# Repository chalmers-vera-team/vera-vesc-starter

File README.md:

# Vera — Starter Motor System

Custom VESC 6-based motor controller developed for the **Vera** Shell Eco-marathon ICE vehicle. It drives a sensored TP Power TP4050 brushless motor through a 6.67:1 belt reduction to reliably crank a rebuilt Honda GX35 4-stroke engine (900–1,200 RPM) at ultra-low energy consumption (<30 Joules per start).

## Overview

* **HW/**: KiCad design files for the custom 4-layer STM32F405 + TI DRV8323RS motor controller (`HW/vera_vesc_starter.kicad_pro`).
* **SW/**: [VEDDERB BLDC Firmware](https://github.com/vedderb/bldc) tracked as a Git submodule.

## Quick Start

Mjau

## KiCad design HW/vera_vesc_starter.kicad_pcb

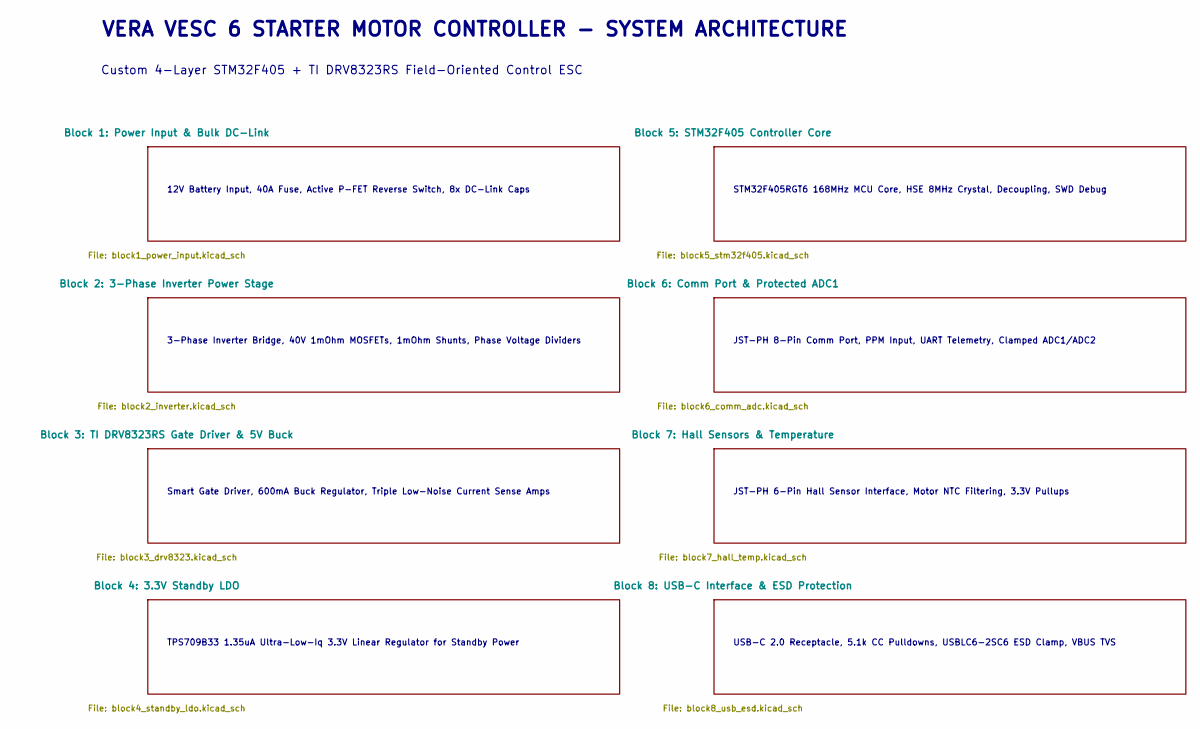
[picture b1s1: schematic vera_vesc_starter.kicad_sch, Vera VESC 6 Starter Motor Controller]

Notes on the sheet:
Smart Gate Driver, 600mA Buck Regulator, Triple Low-Noise Current Sense Amps
TPS709B33 1.35uA Ultra-Low-Iq 3.3V Linear Regulator for Standby Power
USB-C 2.0 Receptacle, 5.1k CC Pulldowns, USBLC6-2SC6 ESD Clamp, VBUS TVS
STM32F405RGT6 168MHz MCU Core, HSE 8MHz Crystal, Decoupling, SWD Debug
Custom 4-Layer STM32F405 + TI DRV8323RS Field-Oriented Control ESC
3-Phase Inverter Bridge, 40V 1mOhm MOSFETs, 1mOhm Shunts, Phase Voltage Dividers
VERA VESC 6 STARTER MOTOR CONTROLLER - SYSTEM ARCHITECTURE
JST-PH 8-Pin Comm Port, PPM Input, UART Telemetry, Clamped ADC1/ADC2
12V Battery Input, 40A Fuse, Active P-FET Reverse Switch, 8x DC-Link Caps
JST-PH 6-Pin Hall Sensor Interface, Motor NTC Filtering, 3.3V Pullups

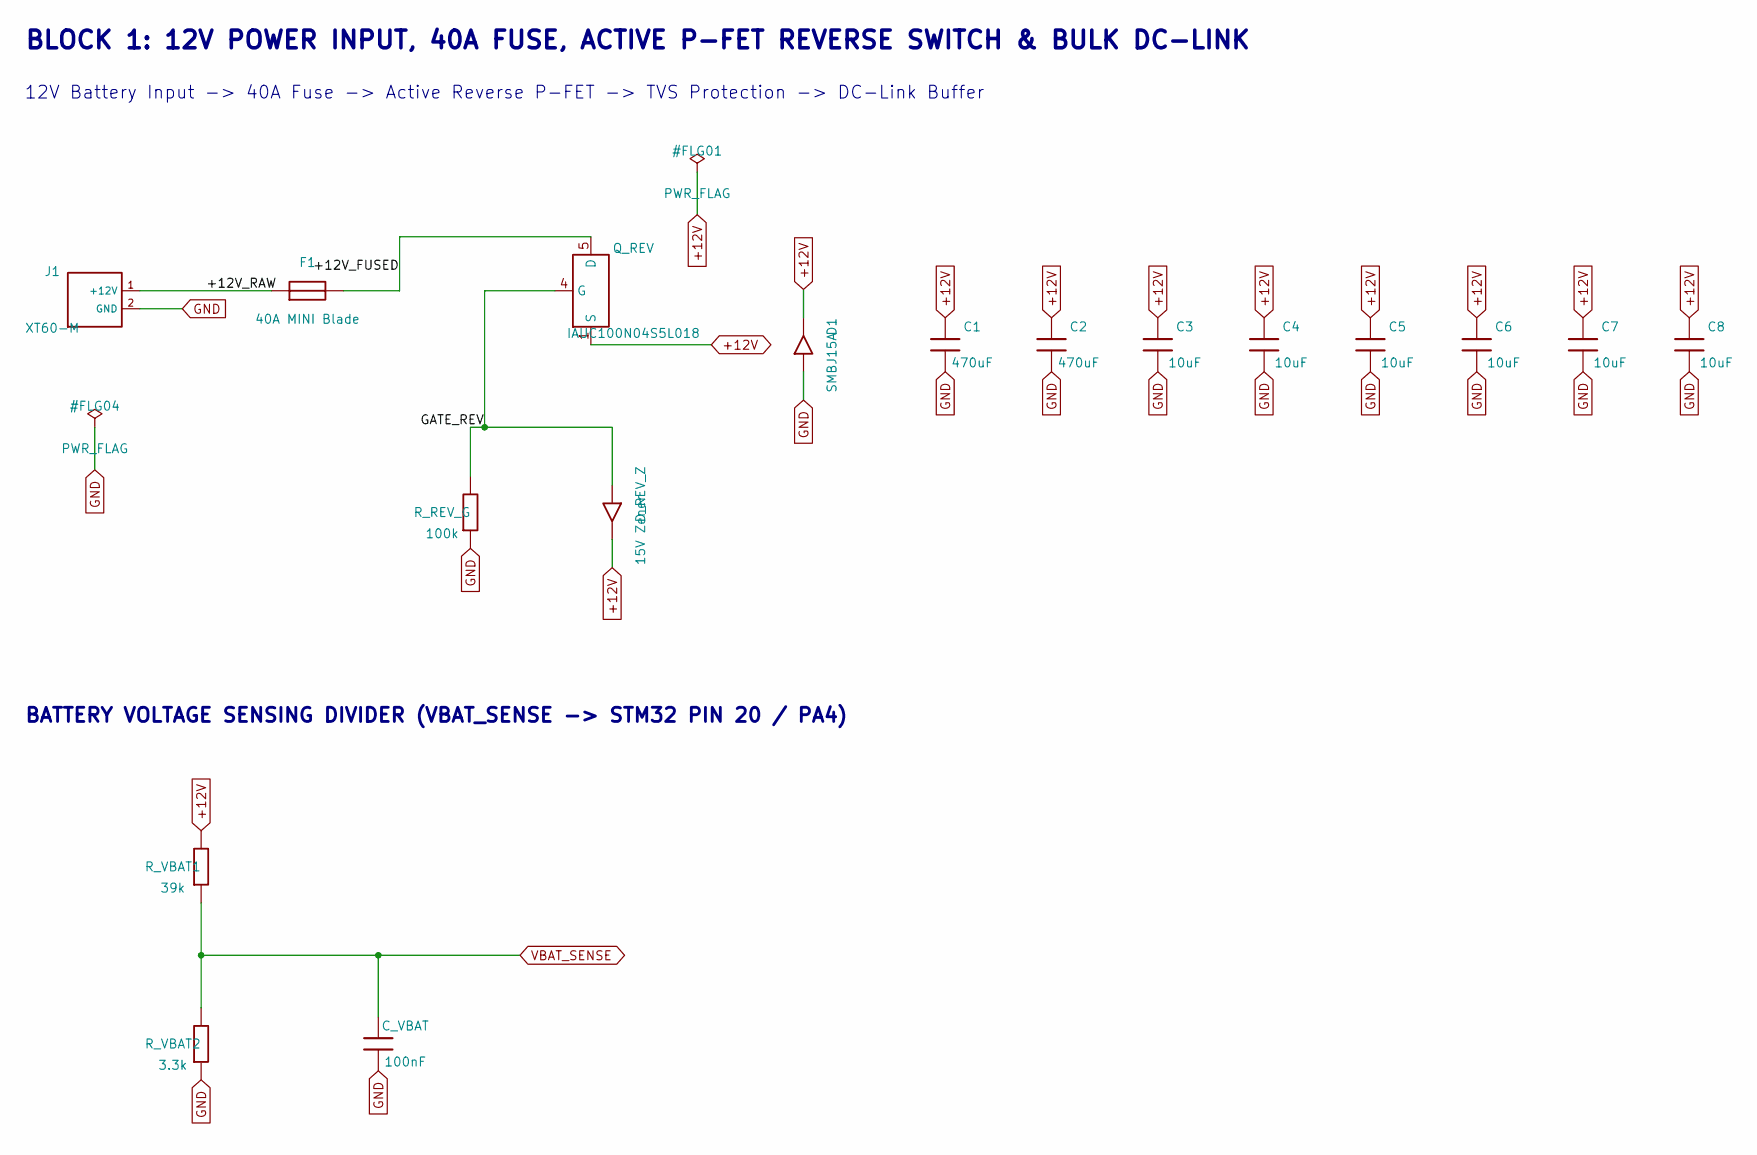
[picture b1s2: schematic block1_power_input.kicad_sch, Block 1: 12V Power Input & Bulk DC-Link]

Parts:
C1, C2: 470uF; CP_Elec_10x10.5; MPN EEH-ZK1V471P
C3, C4, C5, C6, C7, C8: 10uF; C_1206_3216Metric; MPN C1206C106K5RAC7800
C_VBAT: 100nF; C_0603_1608Metric; MPN CC0603KRX7R9BB104
D1: SMBJ15A; D_SMB; MPN SMBJ15A-E3/52
D_REV_Z: 15V Zener; D_SOD-123; MPN MMSZ5245B
F1: 40A MINI Blade; Fuseholder_Blade_Mini_Keystone_3568; MPN Keystone 3568
J1: XT60-M; AMASS_XT60-M_1x02_P7.20mm_Vertical; MPN AMASS-XT60-M
Q_REV: IAUC100N04S5L018; Infineon_PG-TDSON-8_6.15x5.15mm; MPN IAUC100N04S5L018
R_REV_G: 100k; R_0603_1608Metric; MPN RC0603FR-07100KL
R_VBAT1: 39k; R_0603_1608Metric; MPN RC0603FR-0739KL
R_VBAT2: 3.3k; R_0603_1608Metric; MPN RC0603FR-073K3L

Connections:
+12V: C1.1, C2.1, C3.1, C4.1, C5.1, C6.1, C7.1, C8.1, D1.2 (K), D_REV_Z.2 (K), Q_REV.1 (S), Q_REV.2, Q_REV.3, R_VBAT1.1; also elsewhere on the board
+12V_FUSED: F1.2, Q_REV.5 (D)
+12V_RAW: F1.1, J1.1 (+12V)
GATE_REV: D_REV_Z.1 (A), Q_REV.4 (G), R_REV_G.1
GND: C1.2, C2.2, C3.2, C4.2, C5.2, C6.2, C7.2, C8.2, C_VBAT.2, D1.1 (A), J1.2 (GND), R_REV_G.2, R_VBAT2.2; also elsewhere on the board
VBAT_SENSE: C_VBAT.1, R_VBAT1.2, R_VBAT2.1; also elsewhere on the board

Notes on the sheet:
12V Battery Input -> 40A Fuse -> Active Reverse P-FET -> TVS Protection -> DC-Link Buffer
BATTERY VOLTAGE SENSING DIVIDER (VBAT_SENSE -> STM32 PIN 20 / PA4)
BLOCK 1: 12V POWER INPUT, 40A FUSE, ACTIVE P-FET REVERSE SWITCH & BULK DC-LINK

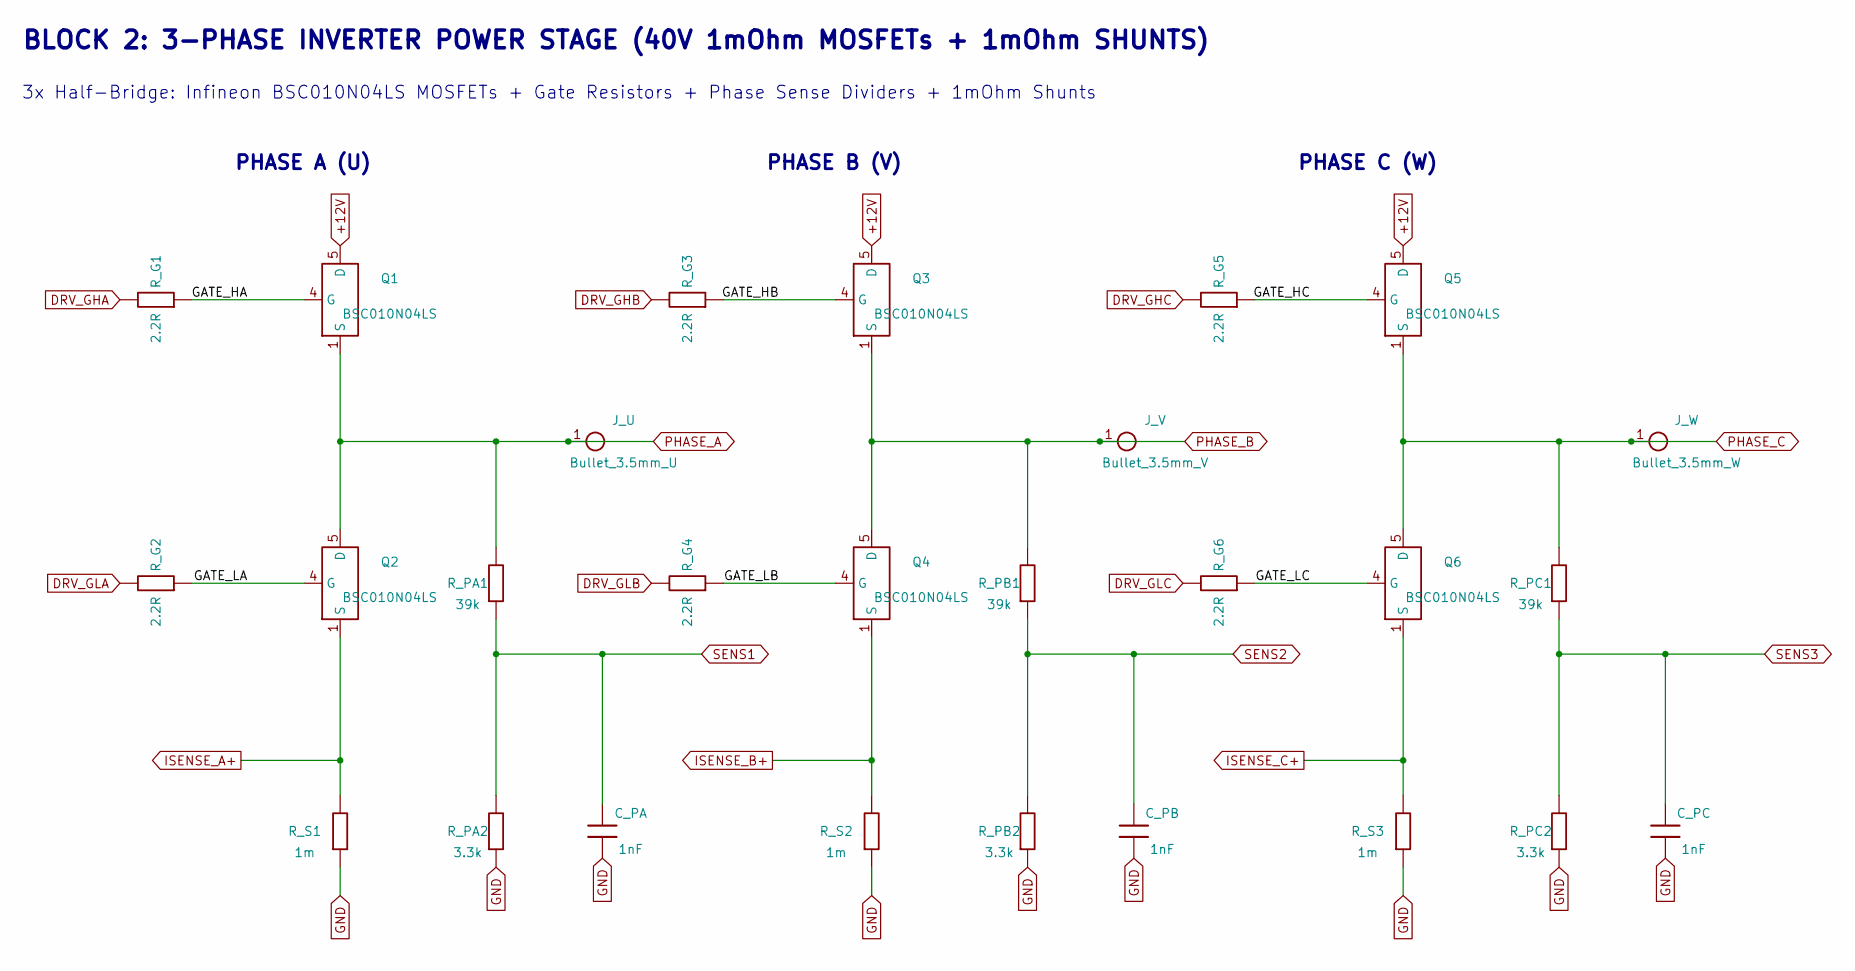
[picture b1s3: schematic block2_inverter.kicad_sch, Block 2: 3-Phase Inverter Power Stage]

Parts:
C_PA: 1nF; C_0603_1608Metric; MPN CC0603KRX7R9BB102
C_PB: 1nF; C_0603_1608Metric; MPN CC0603KRX7R9BB102
C_PC: 1nF; C_0603_1608Metric; MPN CC0603KRX7R9BB102
J_U: Bullet_3.5mm_U; SolderWire-2.5sqmm_1x01_D2.4mm_OD4.4mm; MPN BULLET-3.5MM-F
J_V: Bullet_3.5mm_V; SolderWire-2.5sqmm_1x01_D2.4mm_OD4.4mm; MPN BULLET-3.5MM-F
J_W: Bullet_3.5mm_W; SolderWire-2.5sqmm_1x01_D2.4mm_OD4.4mm; MPN BULLET-3.5MM-F
Q1, Q2, Q3, Q4, Q5, Q6: BSC010N04LS; Infineon_PG-TDSON-8_6.15x5.15mm; MPN BSC010N04LSATMA1
R_G1, R_G2, R_G3, R_G4, R_G5, R_G6: 2.2R; R_0603_1608Metric; MPN RC0603FR-072R2L
R_PA1: 39k; R_0603_1608Metric; MPN RC0603FR-0739KL
R_PA2: 3.3k; R_0603_1608Metric; MPN RC0603FR-073K3L
R_PB1: 39k; R_0603_1608Metric; MPN RC0603FR-0739KL
R_PB2: 3.3k; R_0603_1608Metric; MPN RC0603FR-073K3L
R_PC1: 39k; R_0603_1608Metric; MPN RC0603FR-0739KL
R_PC2: 3.3k; R_0603_1608Metric; MPN RC0603FR-073K3L
R_S1, R_S2, R_S3: 1m; R_2512_6332Metric; MPN WSLP25121L000FEA

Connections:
+12V: Q1.5 (D), Q3.5 (D), Q5.5 (D); also elsewhere on the board
DRV_GHA: R_G1.1; also elsewhere on the board
DRV_GHB: R_G3.1; also elsewhere on the board
DRV_GHC: R_G5.1; also elsewhere on the board
DRV_GLA: R_G2.1; also elsewhere on the board
DRV_GLB: R_G4.1; also elsewhere on the board
DRV_GLC: R_G6.1; also elsewhere on the board
GATE_HA: Q1.4 (G), R_G1.2
GATE_HB: Q3.4 (G), R_G3.2
GATE_HC: Q5.4 (G), R_G5.2
GATE_LA: Q2.4 (G), R_G2.2
GATE_LB: Q4.4 (G), R_G4.2
GATE_LC: Q6.4 (G), R_G6.2
GND: C_PA.2, C_PB.2, C_PC.2, R_PA2.2, R_PB2.2, R_PC2.2, R_S1.2, R_S2.2, R_S3.2; also elsewhere on the board
ISENSE_A+: Q2.1 (S), Q2.2, Q2.3, R_S1.1; also elsewhere on the board
ISENSE_B+: Q4.1 (S), Q4.2, Q4.3, R_S2.1; also elsewhere on the board
ISENSE_C+: Q6.1 (S), Q6.2, Q6.3, R_S3.1; also elsewhere on the board
PHASE_A: J_U.1, Q1.1 (S), Q1.2, Q1.3, Q2.5 (D), R_PA1.1; also elsewhere on the board
PHASE_B: J_V.1, Q3.1 (S), Q3.2, Q3.3, Q4.5 (D), R_PB1.1; also elsewhere on the board
PHASE_C: J_W.1, Q5.1 (S), Q5.2, Q5.3, Q6.5 (D), R_PC1.1; also elsewhere on the board
SENS1: C_PA.1, R_PA1.2, R_PA2.1; also elsewhere on the board
SENS2: C_PB.1, R_PB1.2, R_PB2.1; also elsewhere on the board
SENS3: C_PC.1, R_PC1.2, R_PC2.1; also elsewhere on the board

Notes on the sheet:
BLOCK 2: 3-PHASE INVERTER POWER STAGE (40V 1mOhm MOSFETs + 1mOhm SHUNTS)
PHASE B (V)
PHASE C (W)
PHASE A (U)
3x Half-Bridge: Infineon BSC010N04LS MOSFETs + Gate Resistors + Phase Sense Dividers + 1mOhm Shunts

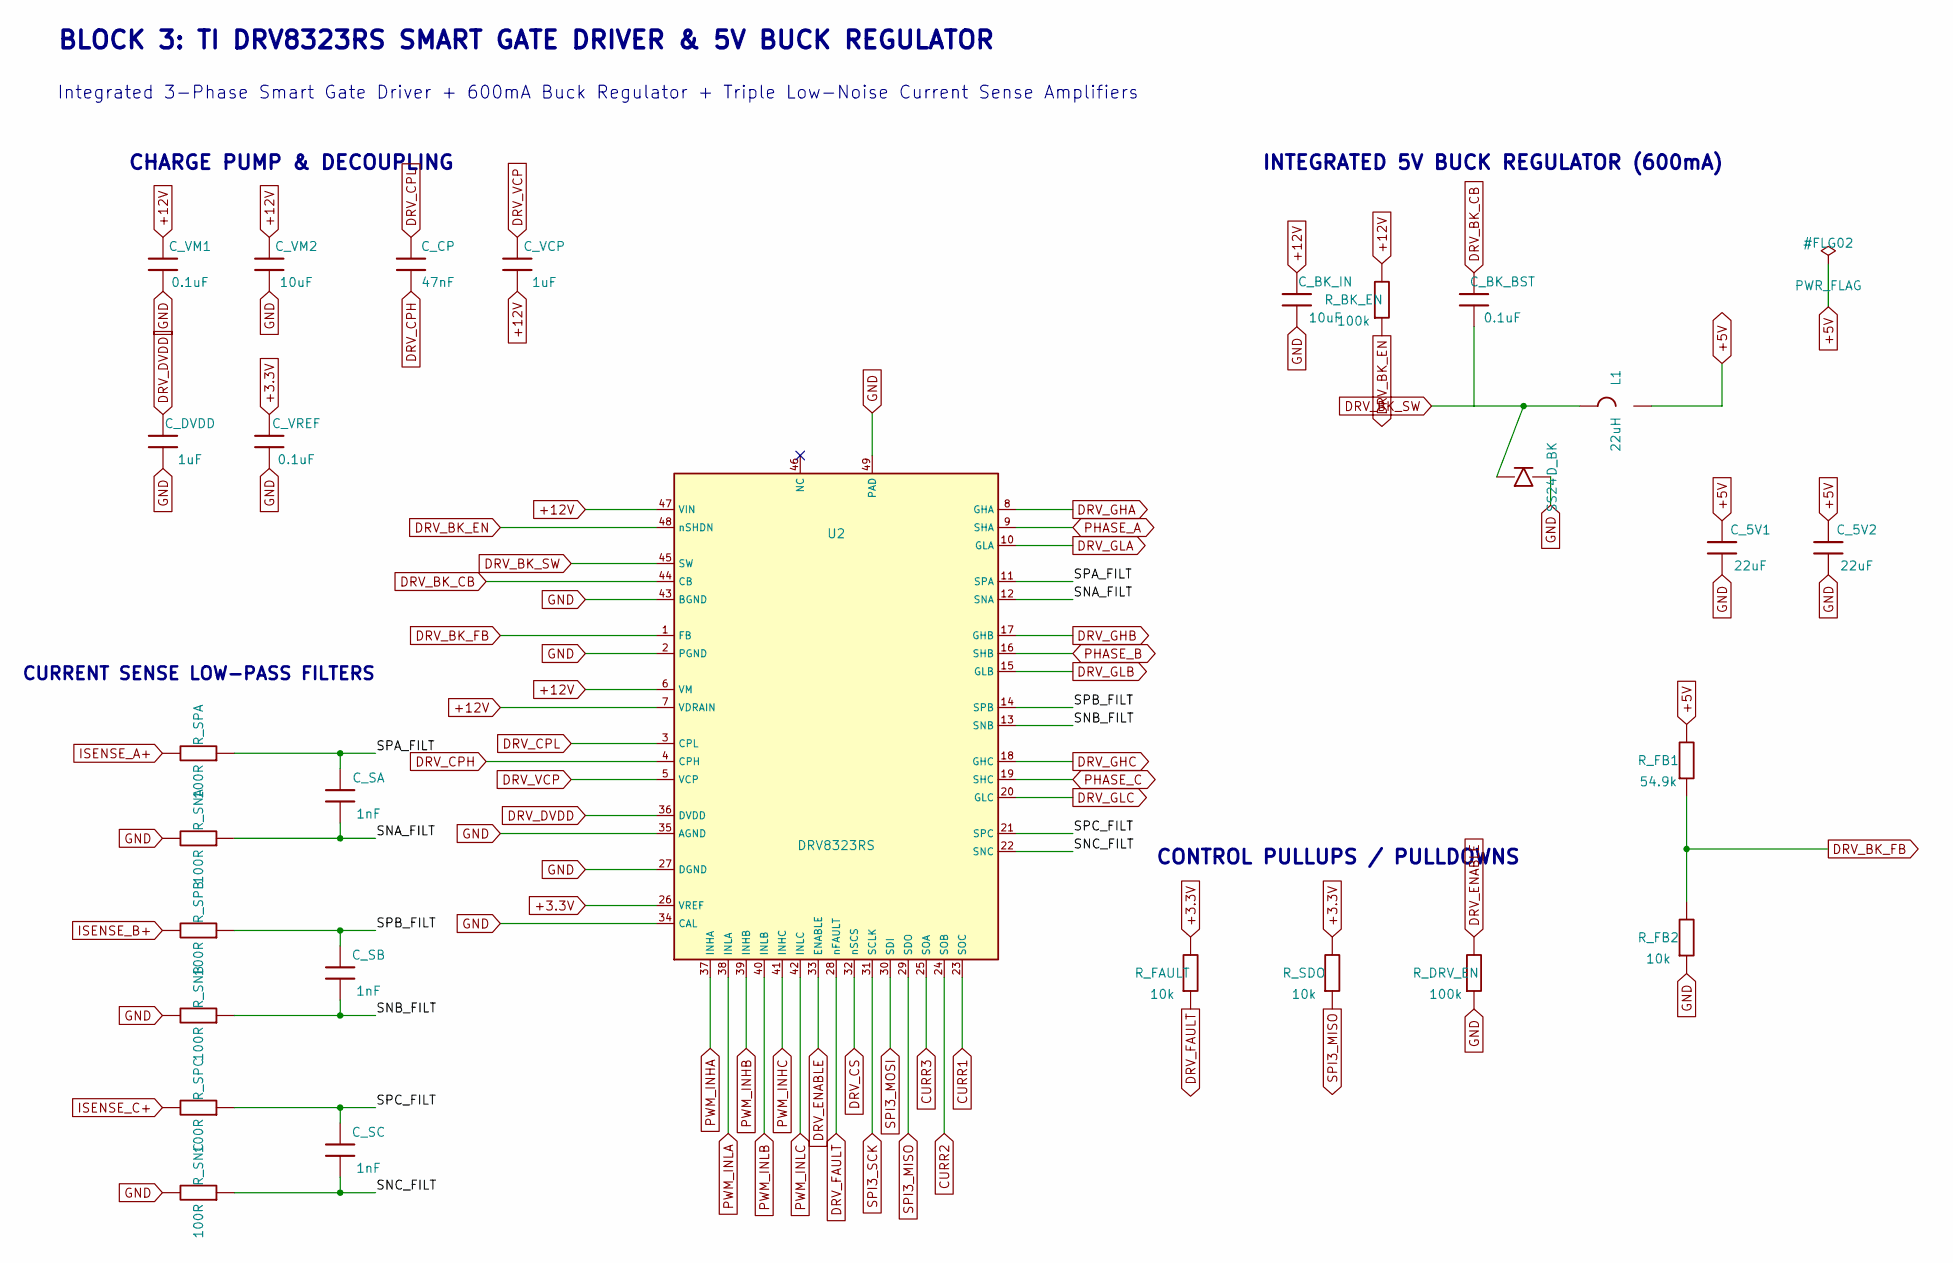
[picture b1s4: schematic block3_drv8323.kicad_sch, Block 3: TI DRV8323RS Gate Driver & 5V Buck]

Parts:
C_5V1, C_5V2: 22uF; C_0805_2012Metric; MPN CL21A226KOQNNNE
C_BK_BST: 0.1uF; C_0603_1608Metric; MPN CC0603KRX7R8BB104
C_BK_IN: 10uF; C_0805_2012Metric; MPN CL21A106KAYNNNE
C_CP: 47nF; C_0603_1608Metric; MPN CC0603KRX7R9BB473
C_DVDD: 1uF; C_0603_1608Metric; MPN CC0603KRX7R7BB105
C_SA: 1nF; C_0603_1608Metric; MPN CC0603KRX7R9BB102
C_SB: 1nF; C_0603_1608Metric; MPN CC0603KRX7R9BB102
C_SC: 1nF; C_0603_1608Metric; MPN CC0603KRX7R9BB102
C_VCP: 1uF; C_0603_1608Metric; MPN CC0603KRX7R7BB105
C_VM1: 0.1uF; C_0603_1608Metric; MPN CC0603KRX7R9BB104
C_VM2: 10uF; C_1206_3216Metric; MPN C1206C106K5RAC7800
C_VREF: 0.1uF; C_0603_1608Metric; MPN CC0603KRX7R8BB104
D_BK: SS24; D_SMA; MPN SS24
L1: 22uH; L_7.3x7.3_H4.5; MPN SRR7045-220M
R_BK_EN: 100k; R_0603_1608Metric; MPN RC0603FR-07100KL
R_DRV_EN: 100k; R_0603_1608Metric; MPN RC0603FR-07100KL
R_FAULT: 10k; R_0603_1608Metric; MPN RC0603FR-0710KL
R_FB1: 54.9k; R_0603_1608Metric; MPN RC0603FR-0754K9L
R_FB2: 10k; R_0603_1608Metric; MPN RC0603FR-0710KL
R_SDO: 10k; R_0603_1608Metric; MPN RC0603FR-0710KL
R_SNA: 100R; R_0603_1608Metric; MPN RC0603FR-07100RL
R_SNB: 100R; R_0603_1608Metric; MPN RC0603FR-07100RL
R_SNC: 100R; R_0603_1608Metric; MPN RC0603FR-07100RL
R_SPA: 100R; R_0603_1608Metric; MPN RC0603FR-07100RL
R_SPB: 100R; R_0603_1608Metric; MPN RC0603FR-07100RL
R_SPC: 100R; R_0603_1608Metric; MPN RC0603FR-07100RL
U2: DRV8323RS; QFN-48-1EP_7x7mm_P0.5mm_EP5.15x5.15mm; MPN DRV8323RSRGZT

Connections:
+3.3V: C_VREF.1, R_FAULT.1, R_SDO.1, U2.26 (VREF); also elsewhere on the board
+5V: C_5V1.1, C_5V2.1, L1.2, R_FB1.1; also elsewhere on the board
+12V: C_BK_IN.1, C_VCP.2, C_VM1.1, C_VM2.1, R_BK_EN.1, U2.6 (VM), U2.7 (VDRAIN), U2.47 (VIN); also elsewhere on the board
CURR1: U2.23 (SOC); also elsewhere on the board
CURR2: U2.24 (SOB); also elsewhere on the board
CURR3: U2.25 (SOA); also elsewhere on the board
DRV_BK_CB: C_BK_BST.2, U2.44 (CB)
DRV_BK_EN: R_BK_EN.2, U2.48 (nSHDN)
DRV_BK_FB: R_FB1.2, R_FB2.1, U2.1 (FB)
DRV_BK_SW: C_BK_BST.1, D_BK.1 (K), L1.1, U2.45 (SW)
DRV_CPH: C_CP.2, U2.4 (CPH)
DRV_CPL: C_CP.1, U2.3 (CPL)
DRV_CS: U2.32 (nSCS); also elsewhere on the board
DRV_DVDD: C_DVDD.1, U2.36 (DVDD)
DRV_ENABLE: R_DRV_EN.1, U2.33 (ENABLE); also elsewhere on the board
DRV_FAULT: R_FAULT.2, U2.28 (nFAULT); also elsewhere on the board
DRV_GHA: U2.8 (GHA); also elsewhere on the board
DRV_GHB: U2.17 (GHB); also elsewhere on the board
DRV_GHC: U2.18 (GHC); also elsewhere on the board
DRV_GLA: U2.10 (GLA); also elsewhere on the board
DRV_GLB: U2.15 (GLB); also elsewhere on the board
DRV_GLC: U2.20 (GLC); also elsewhere on the board
DRV_VCP: C_VCP.1, U2.5 (VCP)
GND: C_5V1.2, C_5V2.2, C_BK_IN.2, C_DVDD.2, C_VM1.2, C_VM2.2, C_VREF.2, D_BK.2 (A), R_DRV_EN.2, R_FB2.2, R_SNA.1, R_SNB.1, R_SNC.1, U2.2 (PGND), U2.27 (DGND), U2.34 (CAL), U2.35 (AGND), U2.43 (BGND), U2.49 (PAD); also elsewhere on the board
ISENSE_A+: R_SPA.1; also elsewhere on the board
ISENSE_B+: R_SPB.1; also elsewhere on the board
ISENSE_C+: R_SPC.1; also elsewhere on the board
PHASE_A: U2.9 (SHA); also elsewhere on the board
PHASE_B: U2.16 (SHB); also elsewhere on the board
PHASE_C: U2.19 (SHC); also elsewhere on the board
PWM_INHA: U2.37 (INHA); also elsewhere on the board
PWM_INHB: U2.39 (INHB); also elsewhere on the board
PWM_INHC: U2.41 (INHC); also elsewhere on the board
PWM_INLA: U2.38 (INLA); also elsewhere on the board
PWM_INLB: U2.40 (INLB); also elsewhere on the board
PWM_INLC: U2.42 (INLC); also elsewhere on the board
SNA_FILT: C_SA.2, R_SNA.2, U2.12 (SNA)
SNB_FILT: C_SB.2, R_SNB.2, U2.13 (SNB)
SNC_FILT: C_SC.2, R_SNC.2, U2.22 (SNC)
SPA_FILT: C_SA.1, R_SPA.2, U2.11 (SPA)
SPB_FILT: C_SB.1, R_SPB.2, U2.14 (SPB)
SPC_FILT: C_SC.1, R_SPC.2, U2.21 (SPC)
SPI3_MISO: R_SDO.2, U2.29 (SDO); also elsewhere on the board
SPI3_MOSI: U2.30 (SDI); also elsewhere on the board
SPI3_SCK: U2.31 (SCLK); also elsewhere on the board

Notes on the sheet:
INTEGRATED 5V BUCK REGULATOR (600mA)
CURRENT SENSE LOW-PASS FILTERS
Integrated 3-Phase Smart Gate Driver + 600mA Buck Regulator + Triple Low-Noise Current Sense Amplifiers
CHARGE PUMP & DECOUPLING
BLOCK 3: TI DRV8323RS SMART GATE DRIVER & 5V BUCK REGULATOR
CONTROL PULLUPS / PULLDOWNS

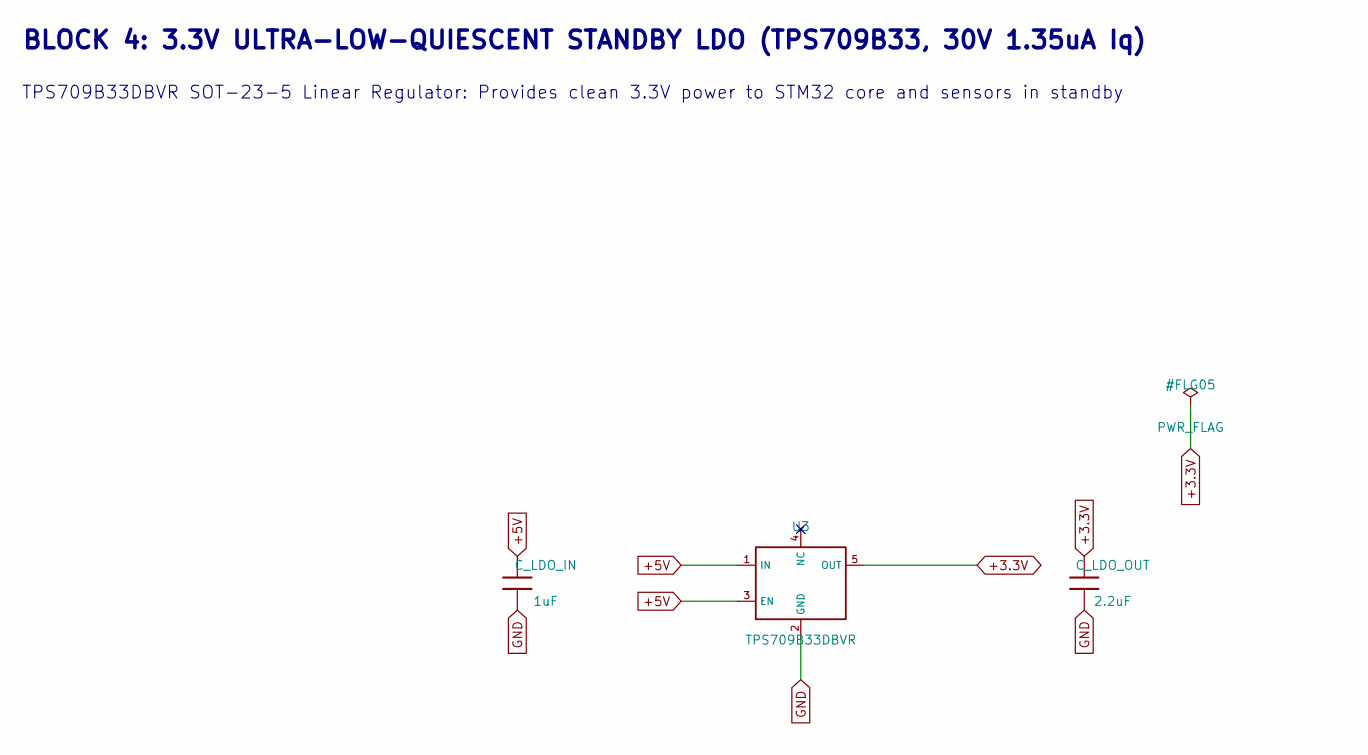
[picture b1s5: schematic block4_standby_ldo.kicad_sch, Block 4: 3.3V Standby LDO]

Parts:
C_LDO_IN: 1uF; C_0603_1608Metric; MPN CC0603KRX7R8BB105
C_LDO_OUT: 2.2uF; C_0603_1608Metric; MPN CC0603KRX7R6BB225
U3: TPS709B33DBVR; SOT-23-5; MPN TPS709B33DBVR

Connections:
+3.3V: C_LDO_OUT.1, U3.5 (OUT); also elsewhere on the board
+5V: C_LDO_IN.1, U3.1 (IN), U3.3 (EN); also elsewhere on the board
GND: C_LDO_IN.2, C_LDO_OUT.2, U3.2 (GND); also elsewhere on the board

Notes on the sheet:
BLOCK 4: 3.3V ULTRA-LOW-QUIESCENT STANDBY LDO (TPS709B33, 30V 1.35uA Iq)
TPS709B33DBVR SOT-23-5 Linear Regulator: Provides clean 3.3V power to STM32 core and sensors in standby

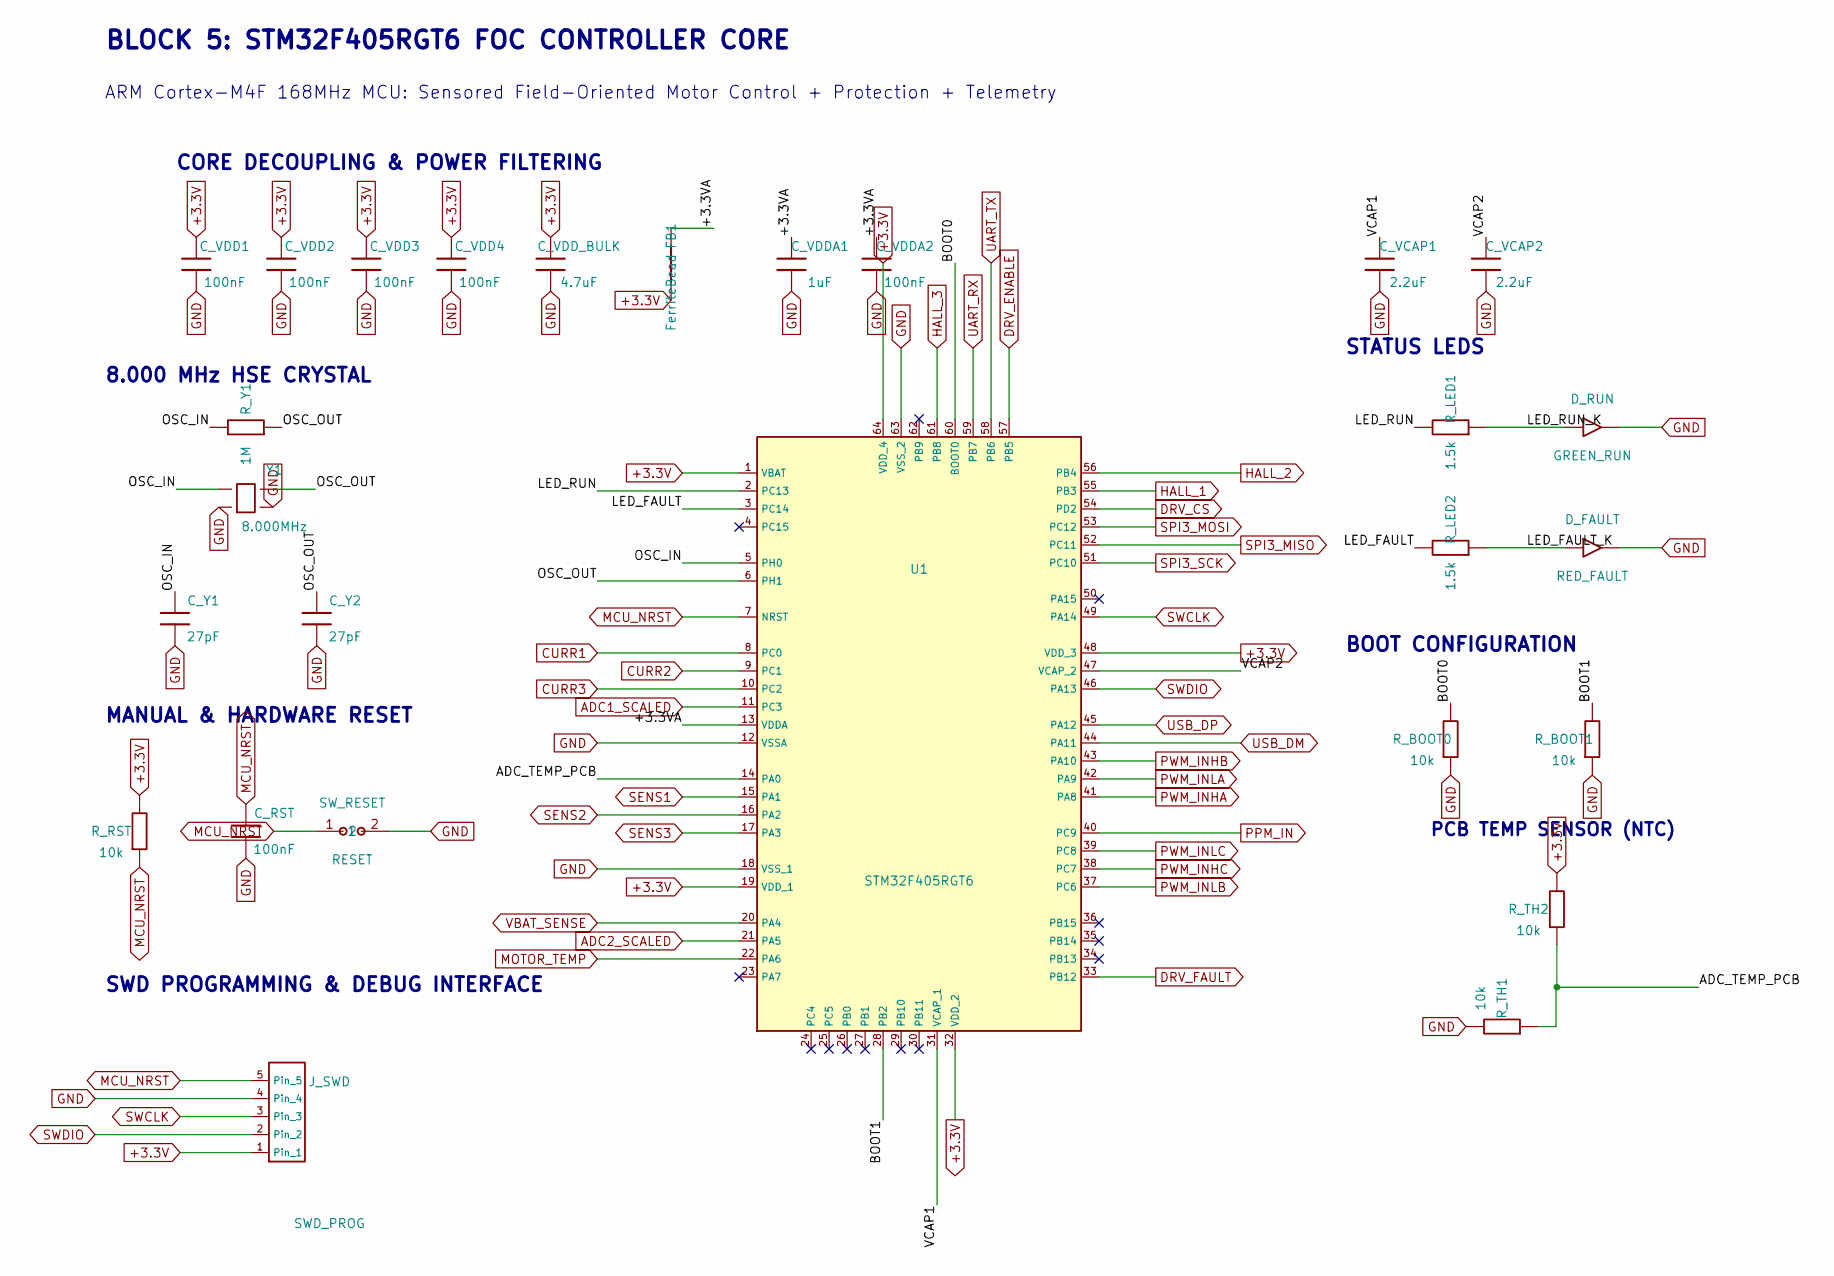
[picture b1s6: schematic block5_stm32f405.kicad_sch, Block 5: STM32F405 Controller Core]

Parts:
C_RST: 100nF; C_0603_1608Metric; MPN CC0603KRX7R9BB104
C_VCAP1, C_VCAP2: 2.2uF; C_0603_1608Metric; MPN CC0603KRX7R6BB225
C_VDD1, C_VDD2, C_VDD3, C_VDD4: 100nF; C_0603_1608Metric; MPN CC0603KRX7R9BB104
C_VDDA1: 1uF; C_0603_1608Metric; MPN CC0603KRX7R7BB105
C_VDDA2: 100nF; C_0603_1608Metric; MPN CC0603KRX7R9BB104
C_VDD_BULK: 4.7uF; C_0805_2012Metric; MPN CL21A475KOQNNNE
C_Y1, C_Y2: 27pF; C_0603_1608Metric; MPN CC0603JRNPO9BN270
D_FAULT: RED_FAULT; LED_0603_1608Metric; MPN LTST-C190KRKT
D_RUN: GREEN_RUN; LED_0603_1608Metric; MPN LTST-C190GKT
FB1: FerriteBead; L_0805_2012Metric; MPN BLM21PG221SN1D
J_SWD: SWD_PROG; PinHeader_1x05_P2.54mm_Vertical; MPN M20-9990546
R_BOOT0, R_BOOT1: 10k; R_0603_1608Metric; MPN RC0603FR-0710KL
R_LED1, R_LED2: 1.5k; R_0603_1608Metric; MPN RC0603FR-071K5L
R_RST: 10k; R_0603_1608Metric; MPN RC0603FR-0710KL
R_TH1: 10k; R_0603_1608Metric; MPN NCP18XH103F03RB
R_TH2: 10k; R_0603_1608Metric; MPN RC0603FR-0710KL
R_Y1: 1M; R_0603_1608Metric; MPN RC0603FR-071ML
SW_RESET: RESET; SW_SPST_PTS645Sx43SMTR92; MPN PTS645SL43-2 LFS
U1: STM32F405RGT6; LQFP-64_10x10mm_P0.5mm; MPN STM32F405RGT6
Y1: 8.000MHz; Crystal_SMD_3225-4Pin_3.2x2.5mm; MPN ABM8-8.000MHZ-B2-T

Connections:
+3.3V: C_VDD1.1, C_VDD2.1, C_VDD3.1, C_VDD4.1, C_VDD_BULK.1, FB1.1, J_SWD.1, R_RST.1, R_TH2.1, U1.1 (VBAT), U1.19 (VDD_1), U1.32 (VDD_2), U1.48 (VDD_3), U1.64 (VDD_4); also elsewhere on the board
+3.3VA: C_VDDA1.1, C_VDDA2.1, FB1.2, U1.13 (VDDA)
ADC1_SCALED: U1.11 (PC3); also elsewhere on the board
ADC2_SCALED: U1.21 (PA5); also elsewhere on the board
ADC_TEMP_PCB: R_TH1.2, R_TH2.2, U1.14 (PA0)
BOOT0: R_BOOT0.1, U1.60 (BOOT0)
BOOT1: R_BOOT1.1, U1.28 (PB2)
CURR1: U1.8 (PC0); also elsewhere on the board
CURR2: U1.9 (PC1); also elsewhere on the board
CURR3: U1.10 (PC2); also elsewhere on the board
DRV_CS: U1.54 (PD2); also elsewhere on the board
DRV_ENABLE: U1.57 (PB5); also elsewhere on the board
DRV_FAULT: U1.33 (PB12); also elsewhere on the board
GND: C_RST.2, C_VCAP1.2, C_VCAP2.2, C_VDD1.2, C_VDD2.2, C_VDD3.2, C_VDD4.2, C_VDDA1.2, C_VDDA2.2, C_VDD_BULK.2, C_Y1.2, C_Y2.2, D_FAULT.2 (K), D_RUN.2 (K), J_SWD.4, R_BOOT0.2, R_BOOT1.2, R_TH1.1, SW_RESET.2, U1.12 (VSSA), U1.18 (VSS_1), U1.63 (VSS_2), Y1.2, Y1.4; also elsewhere on the board
HALL_1: U1.55 (PB3); also elsewhere on the board
HALL_2: U1.56 (PB4); also elsewhere on the board
HALL_3: U1.61 (PB8); also elsewhere on the board
LED_FAULT: R_LED2.1, U1.3 (PC14)
LED_FAULT_K: D_FAULT.1 (A), R_LED2.2
LED_RUN: R_LED1.1, U1.2 (PC13)
LED_RUN_K: D_RUN.1 (A), R_LED1.2
MCU_NRST: C_RST.1, J_SWD.5, R_RST.2, SW_RESET.1, U1.7 (NRST)
MOTOR_TEMP: U1.22 (PA6); also elsewhere on the board
OSC_IN: C_Y1.1, R_Y1.1, U1.5 (PH0), Y1.1
OSC_OUT: C_Y2.1, R_Y1.2, U1.6 (PH1), Y1.3
PPM_IN: U1.40 (PC9); also elsewhere on the board
PWM_INHA: U1.41 (PA8); also elsewhere on the board
PWM_INHB: U1.43 (PA10); also elsewhere on the board
PWM_INHC: U1.38 (PC7); also elsewhere on the board
PWM_INLA: U1.42 (PA9); also elsewhere on the board
PWM_INLB: U1.37 (PC6); also elsewhere on the board
PWM_INLC: U1.39 (PC8); also elsewhere on the board
SENS1: U1.15 (PA1); also elsewhere on the board
SENS2: U1.16 (PA2); also elsewhere on the board
SENS3: U1.17 (PA3); also elsewhere on the board
SPI3_MISO: U1.52 (PC11); also elsewhere on the board
SPI3_MOSI: U1.53 (PC12); also elsewhere on the board
SPI3_SCK: U1.51 (PC10); also elsewhere on the board
SWCLK: J_SWD.3, U1.49 (PA14)
SWDIO: J_SWD.2, U1.46 (PA13)
UART_RX: U1.59 (PB7); also elsewhere on the board
UART_TX: U1.58 (PB6); also elsewhere on the board
USB_DM: U1.44 (PA11); also elsewhere on the board
USB_DP: U1.45 (PA12); also elsewhere on the board
VBAT_SENSE: U1.20 (PA4); also elsewhere on the board
VCAP1: C_VCAP1.1, U1.31 (VCAP_1)
VCAP2: C_VCAP2.1, U1.47 (VCAP_2)

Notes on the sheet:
BLOCK 5: STM32F405RGT6 FOC CONTROLLER CORE
ARM Cortex-M4F 168MHz MCU: Sensored Field-Oriented Motor Control + Protection + Telemetry
CORE DECOUPLING & POWER FILTERING
MANUAL & HARDWARE RESET
PCB TEMP SENSOR (NTC)
BOOT CONFIGURATION
STATUS LEDS
8.000 MHz HSE CRYSTAL
SWD PROGRAMMING & DEBUG INTERFACE

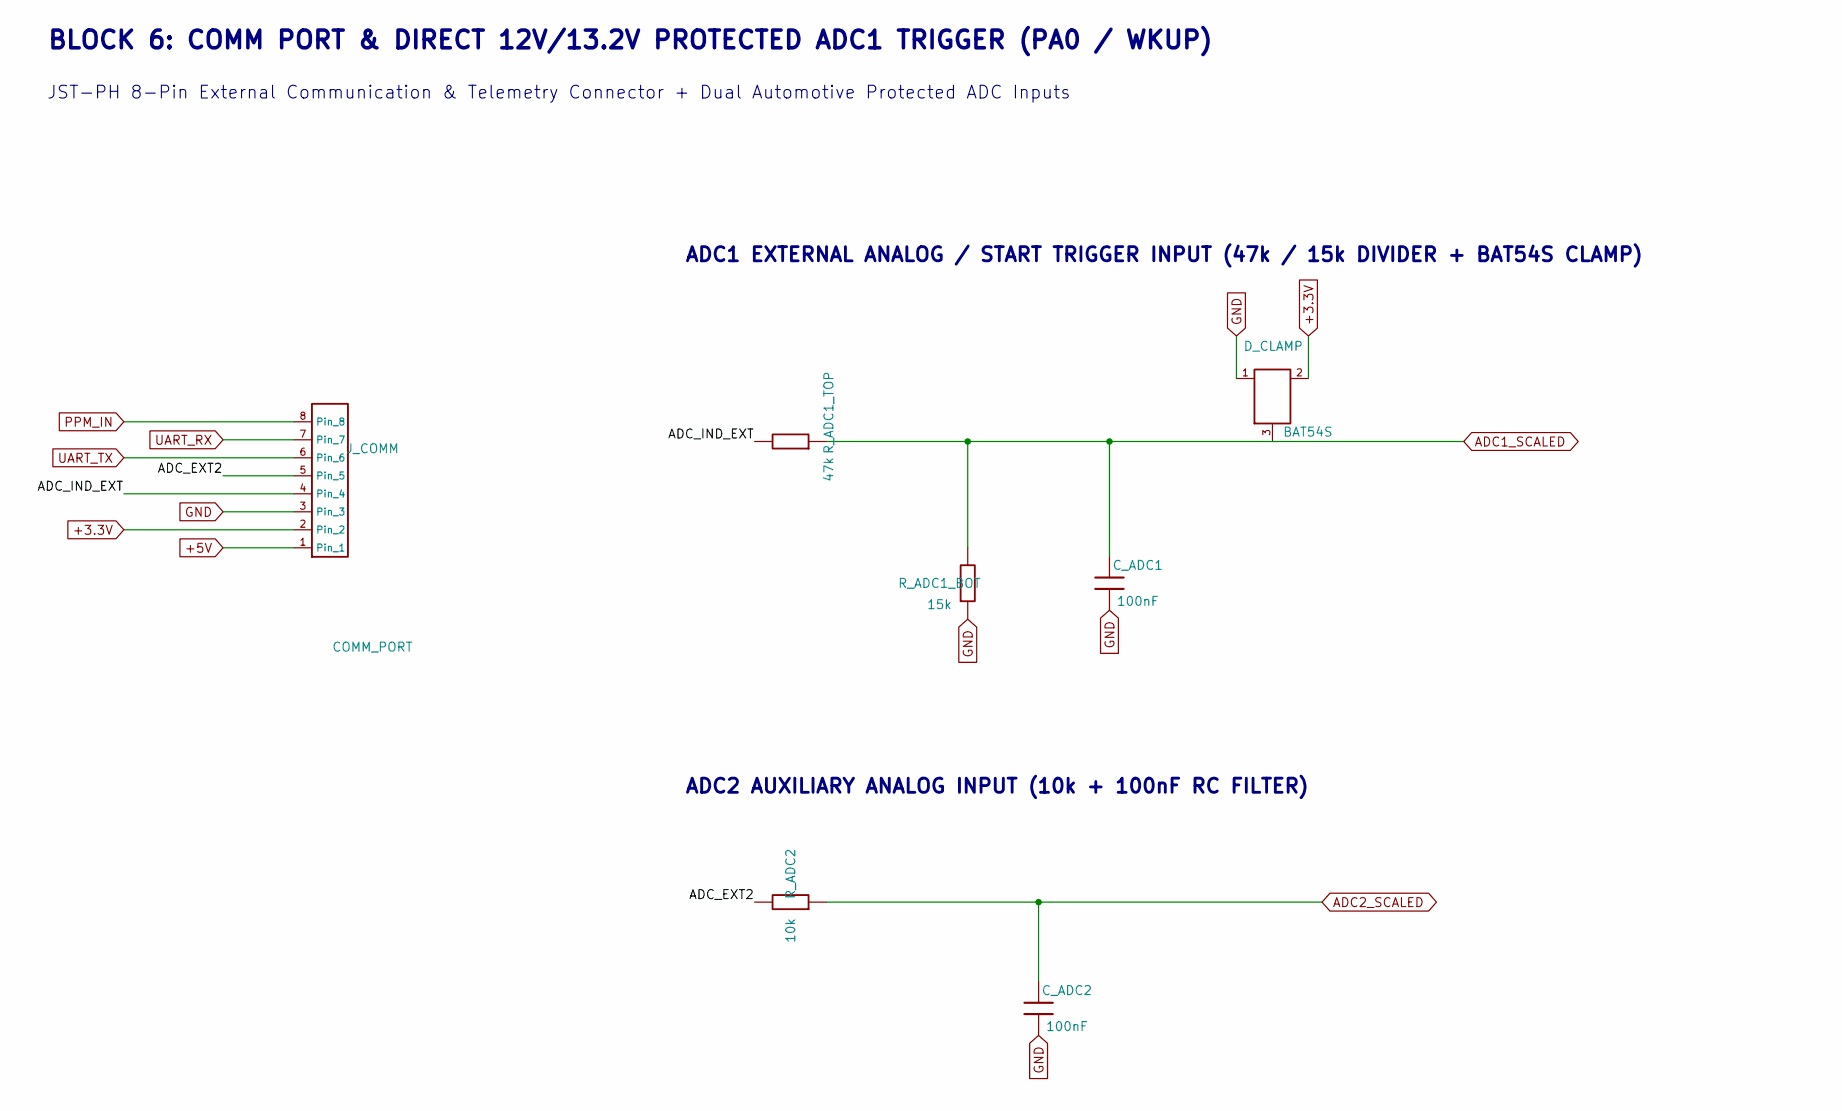
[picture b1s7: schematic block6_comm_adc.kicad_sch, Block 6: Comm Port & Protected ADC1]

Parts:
C_ADC1, C_ADC2: 100nF; C_0603_1608Metric; MPN CC0603KRX7R9BB104
D_CLAMP: BAT54S; SOT-23; MPN BAT54S-7-F
J_COMM: COMM_PORT; JST_PH_B8B-PH-K_1x08_P2.00mm_Vertical; MPN B8B-PH-K-S
R_ADC1_BOT: 15k; R_0603_1608Metric; MPN RC0603FR-0715KL
R_ADC1_TOP: 47k; R_0603_1608Metric; MPN RC0603FR-0747KL
R_ADC2: 10k; R_0603_1608Metric; MPN RC0603FR-0710KL

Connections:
+3.3V: D_CLAMP.2 (Cathode2), J_COMM.2; also elsewhere on the board
+5V: J_COMM.1; also elsewhere on the board
ADC1_SCALED: C_ADC1.1, D_CLAMP.3 (Cath1_An2), R_ADC1_BOT.1, R_ADC1_TOP.2; also elsewhere on the board
ADC2_SCALED: C_ADC2.1, R_ADC2.2; also elsewhere on the board
ADC_EXT2: J_COMM.5, R_ADC2.1
ADC_IND_EXT: J_COMM.4, R_ADC1_TOP.1
GND: C_ADC1.2, C_ADC2.2, D_CLAMP.1 (Anode1), J_COMM.3, R_ADC1_BOT.2; also elsewhere on the board
PPM_IN: J_COMM.8; also elsewhere on the board
UART_RX: J_COMM.7; also elsewhere on the board
UART_TX: J_COMM.6; also elsewhere on the board

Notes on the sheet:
JST-PH 8-Pin External Communication & Telemetry Connector + Dual Automotive Protected ADC Inputs
ADC1 EXTERNAL ANALOG / START TRIGGER INPUT (47k / 15k DIVIDER + BAT54S CLAMP)
ADC2 AUXILIARY ANALOG INPUT (10k + 100nF RC FILTER)
BLOCK 6: COMM PORT & DIRECT 12V/13.2V PROTECTED ADC1 TRIGGER (PA0 / WKUP)
